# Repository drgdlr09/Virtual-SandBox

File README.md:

# Virtual SandBox - A Brief Overview
For Half-Life Week 4, I designed Virtual Sandbox, a pocket-sized desk toy where every pixel on a 0.96" OLED displays acts as a grain of sand. When you tilt or move the device, the sand pours towards whichever side is the lowest, just as real sand would. I wanted to make something simple and satisfying to mess around with, and this was a great way to learn about accelerometers and batteries for the first time. A button on the device allows you change the amount of sand that is displayed, and a toggle switch allows you to turn the device on and off.

# How it Works
Virtual SandBox uses a XIAO ESP32-S3 microcontroller, a 0.96" 128x64 OLED display to display the sand, a LIS3DH accelerometer to track tilt and motion, a push button to change amount of sand, a sliding toggle switch to turn the device on/off, and a 3.7V LiPo battery to power the device.

Virtual SandBox is built around the XIAO ESP32-S3, which was a great fit for this project because it has plenty of memory to simulate thousands of grains of sand at once. It also has battery solder pads which allowed me to make the device portable.

The OLED screen and accelerometer both use I2C, so they share the D4 pin for SDA and D5 pin for SCL.

The button is wired between D0 and ground. Every time you press it, the amount of sand on the screen changes. It cycles between 250, 500, 1000, 2000, and 3000 grains, giving you lots of flexibility to decide how you want to interact with the device.

The battery is the part I'm most proud of. The XIAO's battery pads are on its underside, so I mounted it on header pins to leave a small gap underneath. The battery’s positive wire connects to a pad on the PCB labeled BAT+IN, which runs through the slide switch to another pad labeled BAT+OUT. A short wire goes from there to the BAT+ pad under the XIAO. The battery’s ground wire goes straight to the BAT- pad. This way the switch is soldered to the board instead of hanging off a wire.

*NOTE: When the slide switch is off, the battery is completely disconnected from the XIAO, so it won't charge over USB-C. The switch has to be on while charging.

# The PCB
The PCB is 32x52mm with rounded corners so it's comfortable to hold. It's designed like a stack, with the screen and button on the front and the battery, toggle switch, accelerometer, and ESP32 on the back to give it a clean look. The button is placed in a comfortable position, where your thumb would go if you're holding the device.

# Firmware
The firmware is written in Arduino and uses Adafruit’s PixelDust library for the sand physics. About 45 times a second, it reads the tilt from the accelerometer, moves every grain of sand in that direction, and draws each grain as one pixel on the screen. PixelDust also makes sure grains can’t overlap, so they pile up like real sand instead of passing through each other.

In the firmware folder, you'll also find the code I used to test. This code uses an ESP32 DevKit V1 and an MPU9250.

# Bill of Materials
| Part | Quantity | Unit Price | Total | Vendor |
|---|---|---|---|---|
| XIAO ESP32-S3 | 1 | 6.84 | 6.84 | AliExpress |
| 0.96" OLED Display | 1 | 2.48 | 2.48 | AliExpress |
| LIS3DH Accelerometer | 1 | 1.09 | 1.09 | AliExpress |
| 3.7V LiPo Battery | 1 | 6.02 | 6.02 | AliExpress |
| SS12D00 Slide Switches | 1 | 0.93 | 0.93 | AliExpress |
| Button Set | 1 | 1.09 | 1.09 | AliExpress |
| PCB | 5 | 0.12 | 0.60 | JLCPCB |

**TOTAL PRICE (INCLUDING $11.46 SHIPPING/TAX): $30.51**

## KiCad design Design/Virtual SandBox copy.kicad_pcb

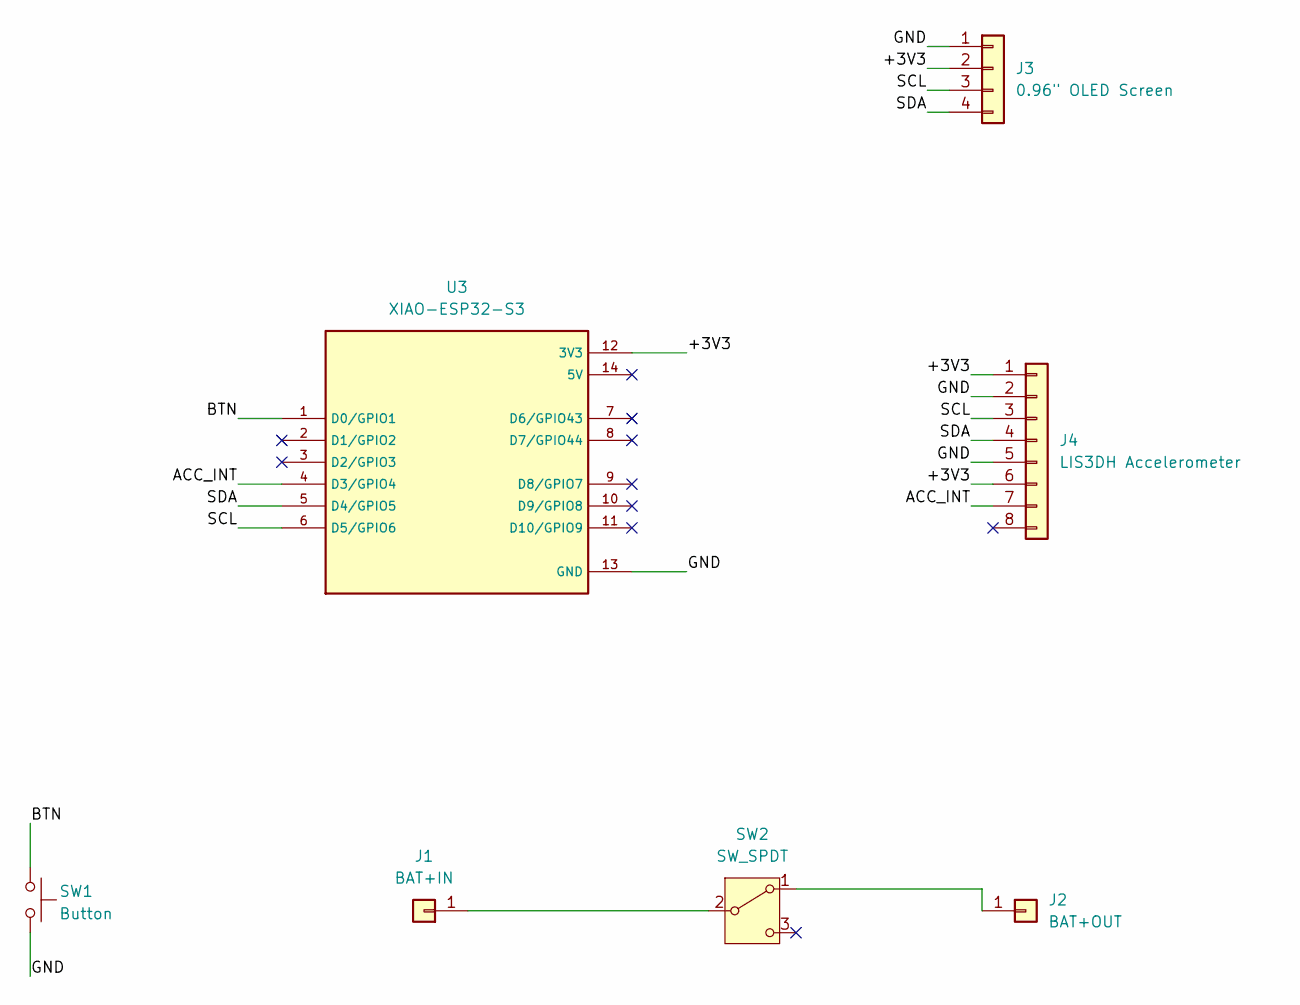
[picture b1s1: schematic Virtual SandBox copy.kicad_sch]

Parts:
J1: BAT+IN; PinHeader_1x01_P2.54mm_Vertical
J2: BAT+OUT; PinHeader_1x01_P2.54mm_Vertical
J3: 0.96" OLED Screen; PinHeader_1x04_P2.54mm_Vertical
J4: LIS3DH Accelerometer; PinHeader_1x08_P2.54mm_Vertical
SW1: Button; SW_PUSH_6mm
SW2: SW_SPDT; PinHeader_1x03_P2.54mm_Vertical
U3: XIAO-ESP32-S3; XIAO ESP32-S3; PARTREV April 22nd, 2026

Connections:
+3V3: J3.2, J4.1, J4.6, U3.12 (3V3)
ACC_INT: J4.7, U3.4 (D3/GPIO4)
BTN: SW1.1, U3.1 (D0/GPIO1)
GND: J3.1, J4.2, J4.5, SW1.2, U3.13 (GND)
N$SW2.1_J2.1: J2.1, SW2.1 (A)
N$SW2.2_J1.1: J1.1, SW2.2 (B)
SCL: J3.3, J4.3, U3.6 (D5/GPIO6)
SDA: J3.4, J4.4, U3.5 (D4/GPIO5)

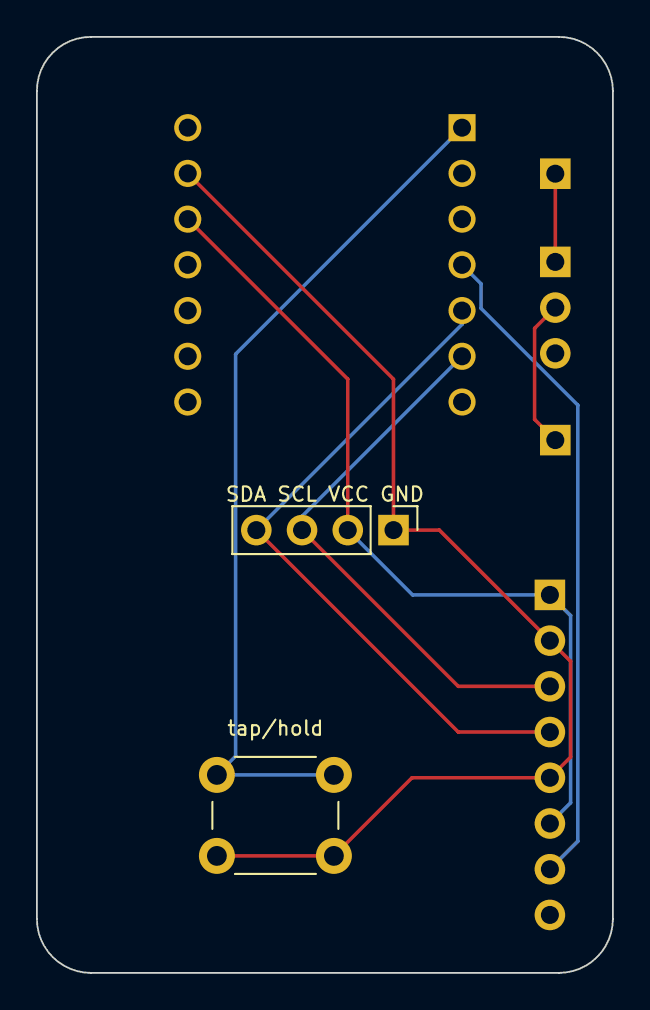
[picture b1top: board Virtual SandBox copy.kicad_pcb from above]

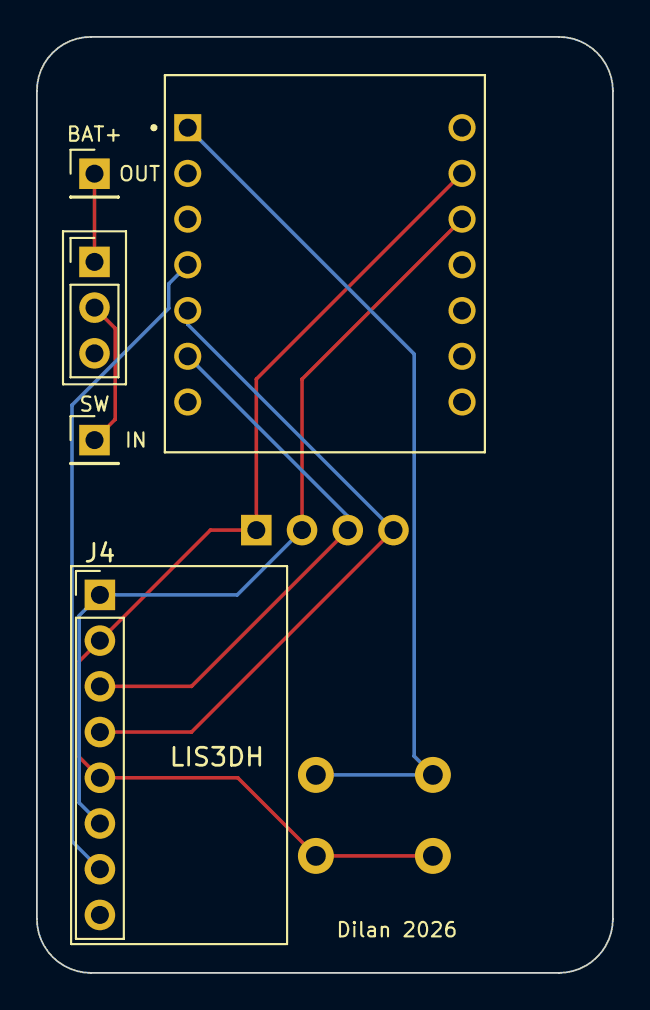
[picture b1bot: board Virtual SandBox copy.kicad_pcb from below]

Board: 2 copper layers, 32.0 x 52.0 mm, 7 parts (5 on the bottom side), 8 nets.

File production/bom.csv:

Designator,Footprint,Quantity,Value,LCSC Part #
J1,PinHeader_1x01_P2.54mm_Vertical,1,BAT+IN,
J2,PinHeader_1x01_P2.54mm_Vertical,1,BAT+OUT,
J3,PinHeader_1x04_P2.54mm_Vertical,1,"0.96\"" OLED Screen",
J4,PinHeader_1x08_P2.54mm_Vertical,1,LIS3DH Accelerometer,
SW1,SW_PUSH_6mm,1,Button,
SW2,PinHeader_1x03_P2.54mm_Vertical,1,SW_SPDT,
U3,XIAO ESP32-S3,1,XIAO-ESP32-S3,
